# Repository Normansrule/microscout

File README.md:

# Wisp: the pocket follow drone

<p>

</p>

Wisp is an open-source drone that knows where it is, avoids crashes and follows you while it films. It is built
from proven, bought parts, so each tier takes an afternoon, and the effort goes into flight software, control
theory and follow-me. It comes with a ground-control app and a site that teaches every algorithm visually.

> [!WARNING]
> **Nothing here has been built, bought or flown.** Wisp is planned by an AI agent and checked by its owner at a
> review gate after every phase. Phase 1 (simulation stack and Control Lab) is waiting for review:
> **[review/P1](review/P1/README.md)** (Phase 0: [review/P0](review/P0/README.md)). Every speed, mass and flight time
> below is an estimate.

## Two airframes, one software stack

"Smallest" and "films good footage while following you" pull against each other, so Wisp comes in two sizes:

| | Wisp Nano | Wisp Follow |
|---|---|---|
| What it is | A Crazyflie 2.1+ kit with optical-flow and ToF (time-of-flight) positioning and obstacle sensors | A 3 inch ducted quad running ArduPilot, with GPS (Global Positioning System), optical flow, lidar for avoidance and a companion computer for vision tracking |
| Mass | about 33-38 g | under 249.48 g with the battery: the Federal Aviation Administration (FAA) registration line for recreational flying |
| Good for | Indoor flying and control-theory experiments, the same day it arrives | Following you outdoors and filming |
| Top speed (estimate) | indoor | 45-61 mph; a 3.5 inch open-frame variant about 71-86 mph |
| Flight time (estimate) | up to 7 min | about 5 min a pack |

100 mph and long flights are out of reach for anything under the registration line: the reasons and the formulas
are in [review/P0/speed.md](review/P0/speed.md).

## Phase 1, in review: simulation stack and Control Lab

- A **ground bridge** between ArduPilot (MAVLink) and the apps, with latency shown and safety rules on what a page
  may command ([software/wisp_gcs](software/wisp_gcs/README.md)).
- The **Control Lab**: the roll-rate loop as a block diagram carrying live numbers, the PID equation with values
  substituted, step response and Bode plot, against a model, a recorded simulation or a live one
  ([docs/control-lab](https://normansrule.github.io/wisp/control-lab/)).
- **Step tests in ArduCopter 4.7.2 SITL** at three gain sets, and a loop model that predicts them, including
  that doubling the gains makes the loop unstable ([review/P1](review/P1/README.md)).

## Phase 0: research and design

- **Research with sources**: Crazyflie kits and decks, sub-250 g ArduPilot builds, ArduPilot follow-me and
  safety features, person tracking on small computers, and the FAA and Los Angeles rules
  ([review/P0/research](review/P0/research/)).
- **Parts lists and gram-by-gram budgets**, generated by a script so the totals add up
  ([review/P0/parts.md](review/P0/parts.md)).
- **Software architecture** and **Ubuntu commands** for ArduPilot SITL (software in the loop) and Gazebo. A first
  simulated follow-me flight has run: ArduCopter 4.7.2 followed a simulated walker for 60 s, a mean 3.85 m behind once settled
  ([review/P0/sitl.md](review/P0/sitl.md)).
- **Three visual concepts** for the app and site, each with a follow-me screen and a live Control Lab:
  [docs/concepts](https://normansrule.github.io/wisp/concepts/).

## Roadmap

| Phase | What | Status |
|---|---|---|
| 0 | Research, parts and weight budgets, architecture, three visual concepts | Done; open questions pending |
| 1 | SITL simulation stack and Control Lab basics | In review |
| 2 | Wisp Nano built and flying, with positioning and avoidance | Not started |
| 3 | Wisp Follow built, tuned and flying with GPS hold | Not started |
| 4 | Safety autopilot: avoidance, crash detection, failsafes | Not started |
| 5 | GPS follow-me, then vision follow-me | Not started |
| 6 | Advanced control: LQR (linear-quadratic regulator), MPC (model predictive control), system identification | Not started |
| 7 | App polish, website, release | Not started |

Simulation comes before hardware and a tether before free flight; no safety test is skipped.

## Also here

- **[Flight Lab](https://normansrule.github.io/wisp/lab/)**: a browser simulator with PID, LQR and MPC autopilots,
  reinforcement learning, an FPV (first-person view) camera and a flight recorder. It came from MicroScout and
  stays as the free-flying 3D playground next to the Control Lab ([docs/guide/lab.md](docs/guide/lab.md)).
- **[archive/microscout](archive/microscout/README.md)**: MicroScout, this repository's first project, a custom-PCB
  (printed circuit board) drone drafted through gates G1-G3. It is frozen; Wisp reuses its simulator, Flight Lab
  and control material.

## Safety and the law

Wisp is flown recreationally under 49 U.S.C. 44809: pass the free TRUST (The Recreational UAS Safety Test), keep it in sight (follow-me does not
change that), get LAANC (Low Altitude Authorization and Notification Capability) approval in controlled airspace (much of Los Angeles), stay at or below 400 ft, and weigh
it ready to fly. **A monetized vlog is not recreational flying** and falls under Part 107. Local rules close most
public land in San Pedro to hobby drones. Details and sources: [review/P0/research/law.md](review/P0/research/law.md).
This is not legal advice. Charge and store LiPo (lithium-polymer) batteries in a fire-safe bag, and never leave them charging
unattended.

## Licences

Software MIT, documentation CC-BY-SA-4.0, future hardware CERN-OHL-S-2.0 and firmware GPL-3.0: [LICENSES.md](LICENSES.md).

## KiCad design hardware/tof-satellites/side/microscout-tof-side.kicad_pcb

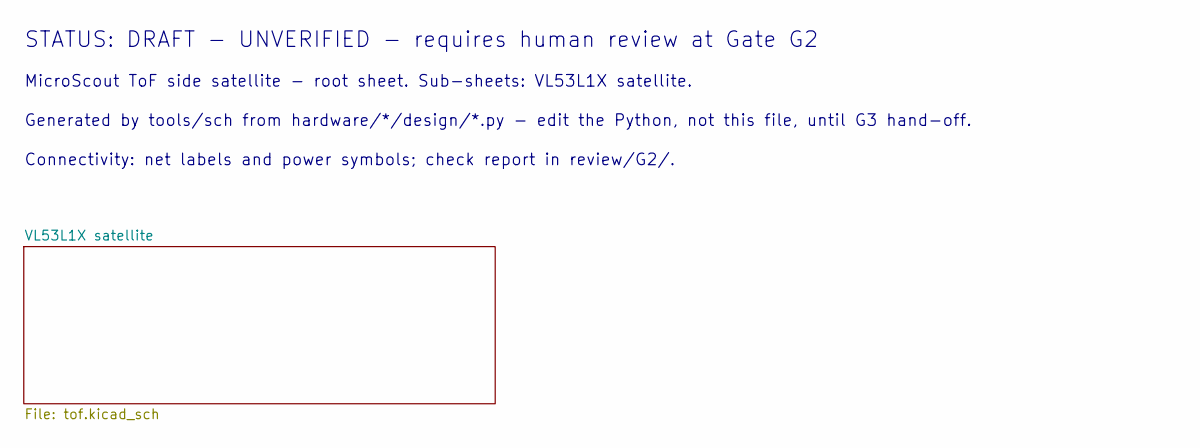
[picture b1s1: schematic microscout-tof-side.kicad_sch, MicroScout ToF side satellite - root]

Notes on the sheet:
STATUS: DRAFT - UNVERIFIED - requires human review at Gate G2
MicroScout ToF side satellite - root sheet. Sub-sheets: VL53L1X satellite.
Generated by tools/sch from hardware/*/design/*.py - edit the Python, not this file, until G3 hand-off.
Connectivity: net labels and power symbols; check report in review/G2/.

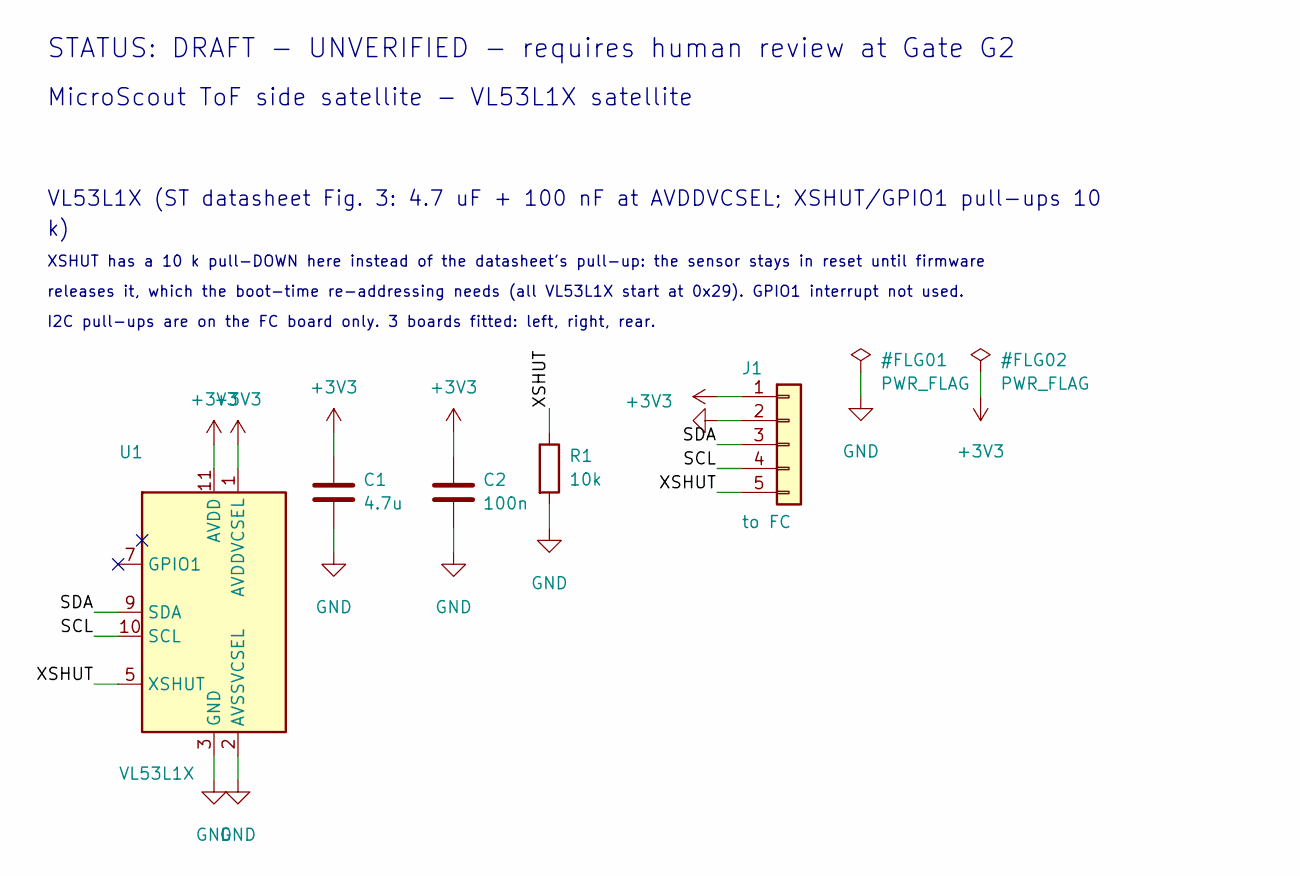
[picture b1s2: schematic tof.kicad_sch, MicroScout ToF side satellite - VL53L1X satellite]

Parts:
C1: 4.7u; C_0402_1005Metric; Rating 10 V X5R; MPN CL05A475MP5NRNC; LCSC C23733
C2: 100n; C_0402_1005Metric; Rating 16 V X7R; MPN CL05B104KO5NNNC; LCSC C1525
J1: to FC; PinHeader_1x05_P1.27mm_Vertical
R1: 10k; R_0402_1005Metric; Rating 1% 62.5 mW; MPN 0402WGF1002TCE; LCSC C25744
U1: VL53L1X; ST_VL53L1x; MPN VL53L1CXV0FY/1; LCSC C190004

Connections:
+3V3: C1.1, C2.1, J1.1, U1.1 (AVDDVCSEL), U1.11 (AVDD)
/VL53L1X satellite/SCL: J1.4, U1.10 (SCL)
/VL53L1X satellite/SDA: J1.3, U1.9 (SDA)
/VL53L1X satellite/XSHUT: J1.5, R1.1, U1.5 (XSHUT)
GND: C1.2, C2.2, J1.2, R1.2, U1.2 (AVSSVCSEL), U1.3 (GND), U1.4 (GND), U1.6 (GND), U1.12 (GND)

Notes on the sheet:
STATUS: DRAFT - UNVERIFIED - requires human review at Gate G2
MicroScout ToF side satellite - VL53L1X satellite
VL53L1X (ST datasheet Fig. 3: 4.7 uF + 100 nF at AVDDVCSEL; XSHUT/GPIO1 pull-ups 10
XSHUT has a 10 k pull-DOWN here instead of the datasheet's pull-up: the sensor stays in reset until firmware
releases it, which the boot-time re-addressing needs (all VL53L1X start at 0x29). GPIO1 interrupt not used.
I2C pull-ups are on the FC board only. 3 boards fitted: left, right, rear.

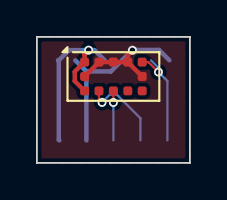
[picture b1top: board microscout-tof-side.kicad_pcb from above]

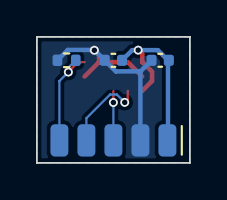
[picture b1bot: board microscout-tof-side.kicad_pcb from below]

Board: 2 copper layers, 8.5 x 7.0 mm, 5 parts (4 on the bottom side), 5 nets.

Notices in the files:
README.md:
Docs licence CC-BY-SA-4.0
hardware/tof-satellites/front/tof.kicad_sch:
MicroScout (open hardware, CERN-OHL-S-2.0)
